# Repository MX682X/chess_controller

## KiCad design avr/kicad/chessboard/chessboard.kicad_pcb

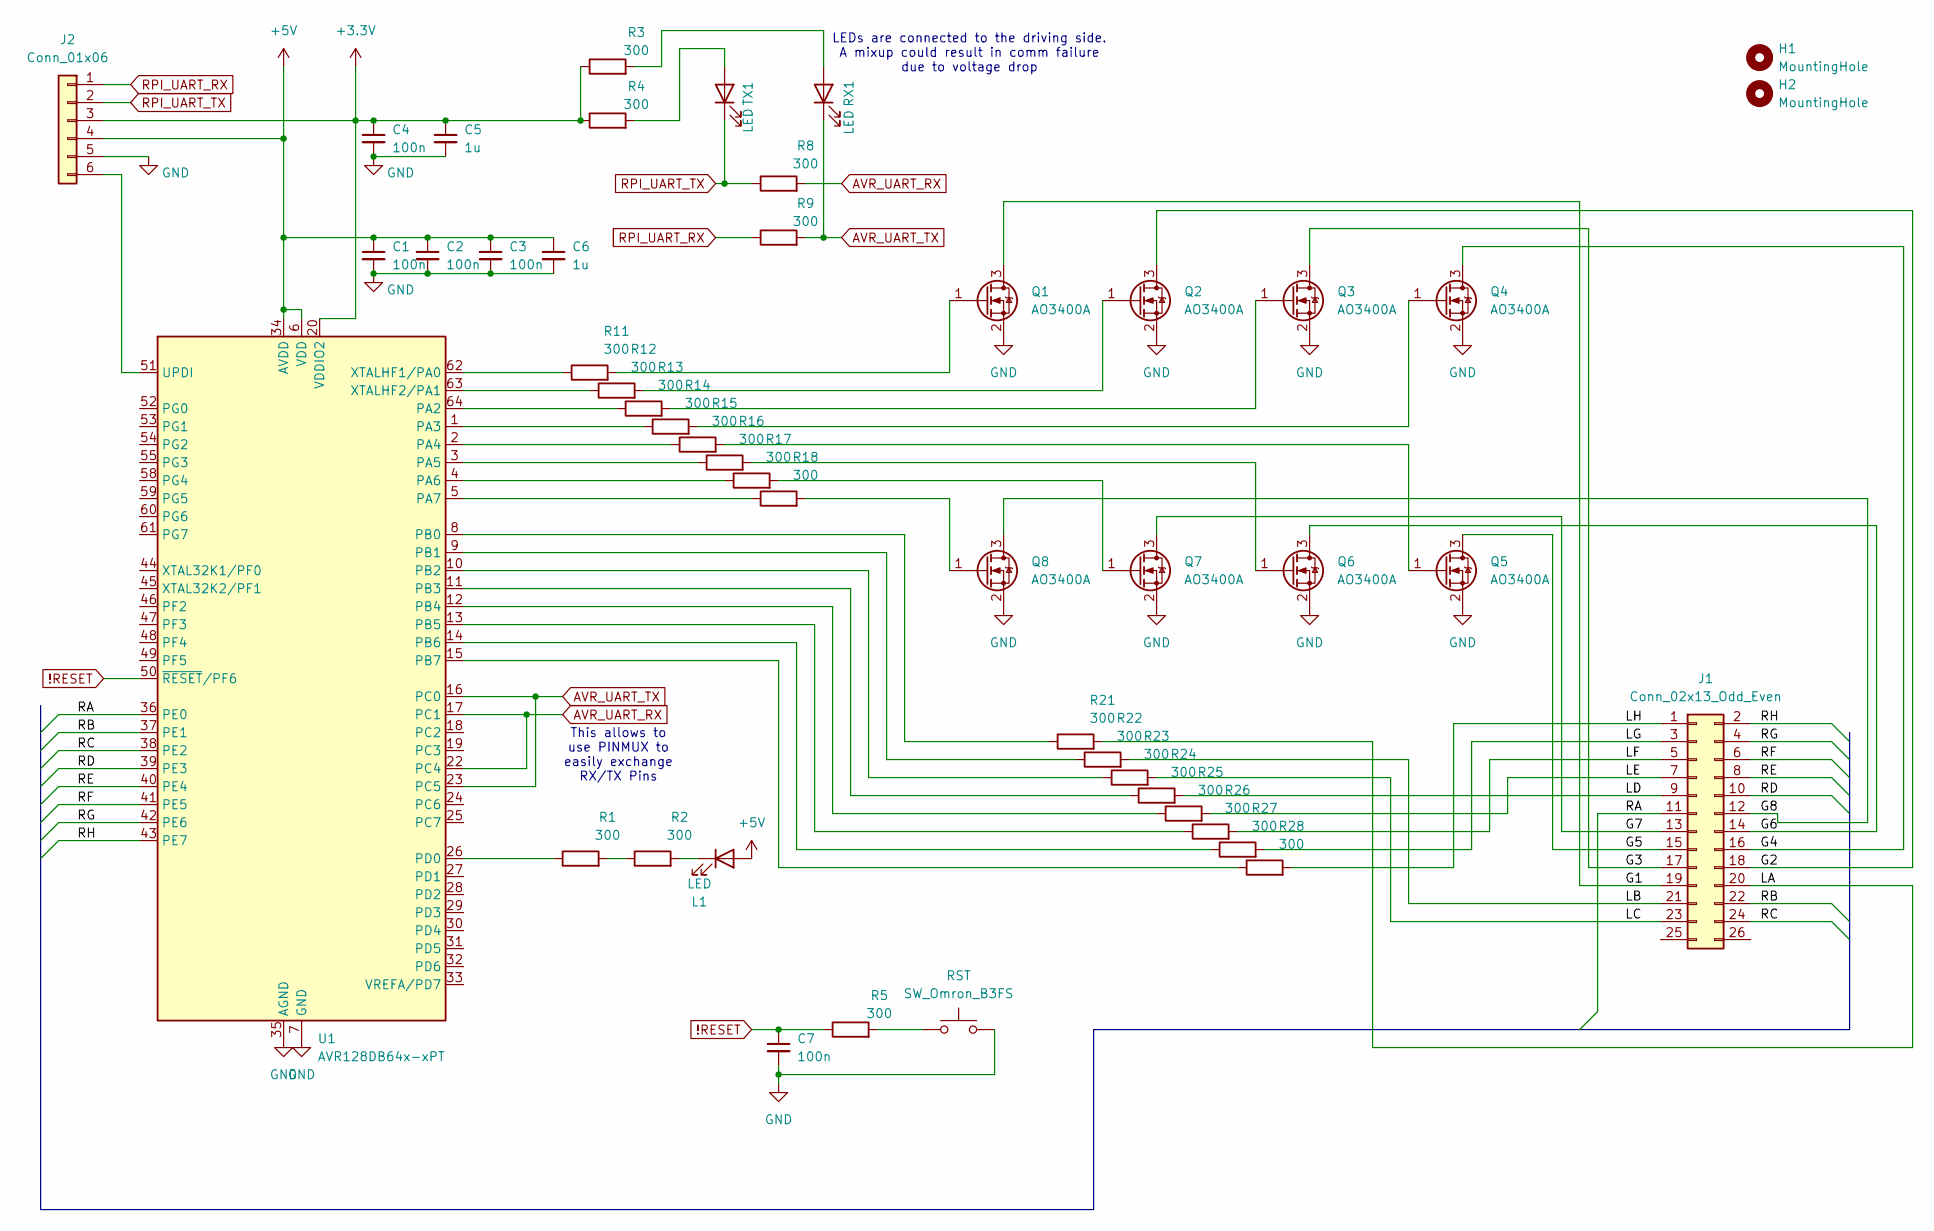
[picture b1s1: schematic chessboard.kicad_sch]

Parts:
C1, C2, C3, C4, C7: 100n; C_0603_1608Metric_Pad1.08x0.95mm_HandSolder
C5, C6: 1u; C_0603_1608Metric_Pad1.08x0.95mm_HandSolder
H1, H2: MountingHole; MountingHole_3.2mm_M3_DIN965
J1: Conn_02x13_Odd_Even; PinHeader_2x13_P2.54mm_Vertical
J2: Conn_01x06; PinSocket_1x06_P2.54mm_Vertical
L1: LED; LED_0603_1608Metric_Pad1.05x0.95mm_HandSolder
Q1, Q2, Q3, Q4, Q5, Q6, Q7, Q8: AO3400A; SOT-23
R1, R2, R3, R4, R5, R8, R9, R11, R12, R13, R14, R15, R16, R17, R18, R21, R22, R23, R24, R25, R26, R27, R28: 300; R_0603_1608Metric_Pad0.98x0.95mm_HandSolder
RST: SW_Omron_B3FS; SW_SPST_Omron_B3FS-100xP
RX1: LED; LED_0603_1608Metric_Pad1.05x0.95mm_HandSolder
TX1: LED; LED_0603_1608Metric_Pad1.05x0.95mm_HandSolder
U1: AVR128DB64x-xPT; TQFP-64_10x10mm_P0.5mm

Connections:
!RESET: C7.1, R5.1, U1.50 (~RESET/PF6)
+3.3V: C4.1, C5.1, J2.3, R3.1, R4.1, U1.20 (VDDIO2)
+5V: C1.1, C2.1, C3.1, C6.1, J2.4, L1.2 (A), U1.6 (VDD), U1.34 (AVDD), U1.56 (VDD)
/G1: J1.19, Q1.3 (D)
/G2: J1.18, Q2.3 (D)
/G3: J1.17, Q3.3 (D)
/G4: J1.16, Q4.3 (D)
/G5: J1.15, Q5.3 (D)
/G6: J1.14, Q6.3 (D)
/G7: J1.13, Q7.3 (D)
/G8: J1.12, Q8.3 (D)
/LA: J1.20, R21.2
/LB: J1.21, R22.2
/LC: J1.23, R23.2
/LD: J1.9, R24.2
/LE: J1.7, R25.2
/LF: J1.5, R26.2
/LG: J1.3, R27.2
/LH: J1.1, R28.2
/RA: J1.11, U1.36 (PE0)
/RB: J1.22, U1.37 (PE1)
/RC: J1.24, U1.38 (PE2)
/RD: J1.10, U1.39 (PE3)
/RE: J1.8, U1.40 (PE4)
/RF: J1.6, U1.41 (PE5)
/RG: J1.4, U1.42 (PE6)
/RH: J1.2, U1.43 (PE7)
AVR_UART_RX: R8.2, U1.17 (PC1), U1.22 (PC4)
AVR_UART_TX: R9.2, RX1.1 (K), U1.16 (PC0), U1.23 (PC5)
GND: C1.2, C2.2, C3.2, C4.2, C5.2, C6.2, C7.2, J2.5, Q1.2 (S), Q2.2 (S), Q3.2 (S), Q4.2 (S), Q5.2 (S), Q6.2 (S), Q7.2 (S), Q8.2 (S), RST.2, U1.7 (GND), U1.21 (GND), U1.35 (AGND), U1.57 (GND)
unnamed: J2.6, U1.51 (UPDI)
unnamed: L1.1 (K), R2.2
unnamed: Q1.1 (G), R11.2
unnamed: Q2.1 (G), R12.2
unnamed: Q3.1 (G), R13.2
unnamed: Q4.1 (G), R14.2
unnamed: Q5.1 (G), R15.2
unnamed: Q6.1 (G), R16.2
unnamed: Q7.1 (G), R17.2
unnamed: Q8.1 (G), R18.2
unnamed: R1.2, R2.1
unnamed: R5.2, RST.1
unnamed: R3.2, RX1.2 (A)
unnamed: R4.2, TX1.2 (A)
unnamed: R13.1, U1.64 (PA2)
unnamed: R14.1, U1.1 (PA3)
unnamed: R15.1, U1.2 (PA4)
unnamed: R16.1, U1.3 (PA5)
unnamed: R17.1, U1.4 (PA6)
unnamed: R18.1, U1.5 (PA7)
unnamed: R21.1, U1.8 (PB0)
unnamed: R22.1, U1.9 (PB1)
unnamed: R23.1, U1.10 (PB2)
unnamed: R24.1, U1.11 (PB3)
unnamed: R25.1, U1.12 (PB4)
unnamed: R26.1, U1.13 (PB5)
unnamed: R27.1, U1.14 (PB6)
unnamed: R28.1, U1.15 (PB7)
unnamed: R1.1, U1.26 (PD0)
unnamed: R11.1, U1.62 (XTALHF1/PA0)
unnamed: R12.1, U1.63 (XTALHF2/PA1)
RPI_UART_RX: J2.1, R9.1
RPI_UART_TX: J2.2, R8.1, TX1.1 (K)

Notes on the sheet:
This allows to use PINMUX to easily exchange RX/TX Pins
LEDs are connected to the driving side. A mixup could result in comm failure due to voltage drop

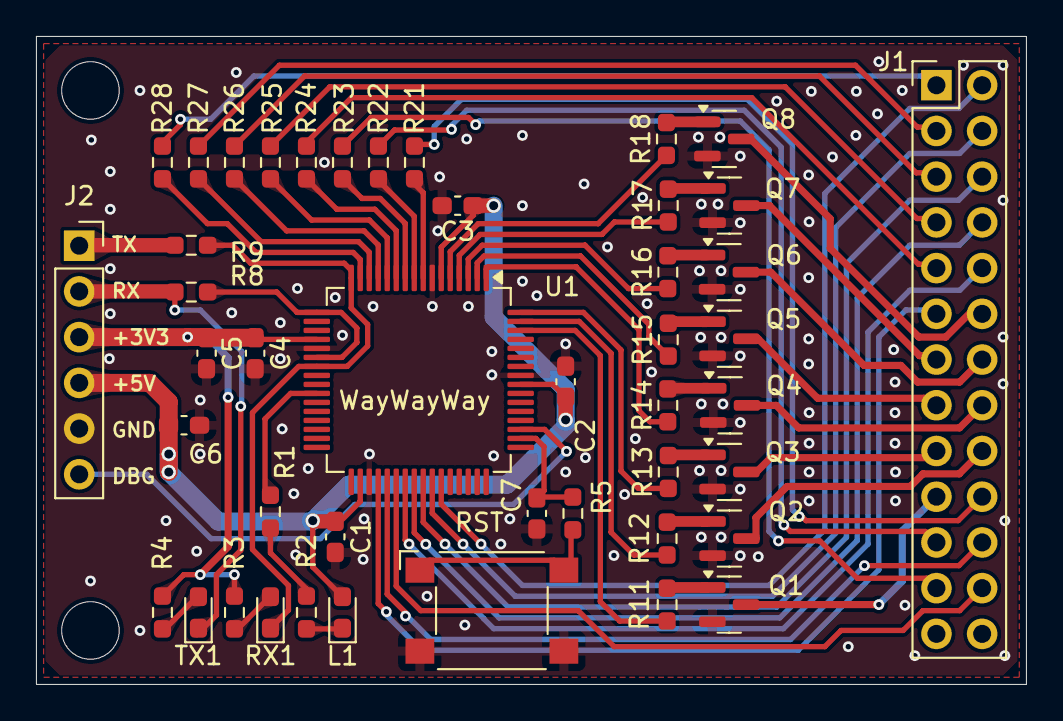
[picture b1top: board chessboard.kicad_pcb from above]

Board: 2 copper layers, 55.0 x 36.0 mm, 47 parts (0 on the bottom side), 63 nets.

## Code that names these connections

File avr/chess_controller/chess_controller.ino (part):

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 * DB-Series
 * AVR64DB64 (optiboot)
 * Clock Speed: 16 MHz, internal
 * Bootloader Serial port: PC0, PC1
 * MVIO: Enabled
 * 
*/ 
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  TCB4.CCMP = 46875;
  TCB4.CTRLA = TCB_CLKSEL_DIV2_gc | TCB_ENABLE_bm;
  
  digitalWriteFast(PIN_PD0, HIGH);  // "disable" LED
  pinConfigure(PIN_PD0, (PIN_DIR_OUT | PIN_INVERT_ON | PIN_ISC_DISABLE));
  digitalWriteFast(PIN_PA0, HIGH);  // init FET loop
  CURR_LINE = 0x00;
  Serial.begin(115200);
  
  Serial.println("Setup Done");
  digitalWriteFast(PIN_PD0, HIGH);  // "Enable" LED

  boot_splash();
}
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    COM_VPORT.OUT = 0x01;             // enable first com transistor
    ACQ_STATUS |= 0x01;               // indicator for "all 8"
    CURR_LINE = 0x00;
    VPORTD.IN |= 0x01;                // activity PD0 (toggle)
  } else {
    LED_VPORT.OUT = current_leds[line];  // load new LED state
    COM_VPORT.OUT = com;              // enable next com transistor
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
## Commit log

2024-10-02 extend gitignore, fix acqusition
2024-10-02 fix commands
2024-10-03 first Python commit
2024-10-04 startpos part 1
2024-10-04 toolbox part 2 (startpos bugged)
2024-10-04 toolbox part 2 (startpos bugged) (again)
2024-10-04 fixed startpos
2024-10-04 startpos moved and changed
2024-10-04 add board to pos
2024-10-06 its alive
2024-10-06 fixed import
2024-10-07 extend command set
2024-10-09 format and match case
2024-10-09 added board simulation gui
2024-10-09 display (untested)
2024-10-10 include display (still untested)
2024-10-14 added CMD Handling (I should really test this)
2024-10-15 fixed CMD Handling (you guessed it: Its still untestet)
2024-10-16 fixed waitforstartpos
2024-10-16 CMD bugfix
2024-10-16 CMD bugfix2
2024-10-16 CMD bugfix 3
2024-10-16 CMD bugfix 4
2024-10-16 CMD bugfix 5
2024-10-16 CMD bugfix 6
2024-10-16 CMD bugfix 7
2024-10-16 CMD bugfix 8
2024-10-16 CMD bugfix 9
2024-10-16 CMD bugfix 10
2024-10-16 CMD bugfix 11
2024-10-16 CMD bugfix 12
2024-10-16 lcd bugfix 1
2024-10-16 lcd bugfix 2
2024-10-16 threading bugfix 1
2024-10-16 threading bugfix 2
2024-10-16 lcd bugfix 3
2024-10-16 lcd bugfix 4
2024-10-16 beauty
2024-10-16 import+display cleanup
2024-10-16 display cleanup (for real)
2024-10-16 added input buffer reset
2024-10-16 reset debug
2024-10-16 reset debuged
2024-10-16 Squash commits
    reset debuged
    reset debug
    added input buffer reset
    display cleanup (for real)
    import+display cleanup
    beauty
2024-10-17 added Playercolors and over Board play
2024-10-23 added pgn export
2024-12-17 first test
2024-12-17 debuging
2024-12-17 debuging 2
2024-12-17 es funktioniert
2024-12-17 implemented stabel command
2024-12-24 cyd init
2024-12-25 added Scene 1_1
2024-12-25 fixed cb functions
2024-12-25 added transition
2025-01-10 added lv config
2025-01-10 new cyd
2025-01-12 added \n
2025-01-12 stopping with exitflag
2025-01-12 idk 4
2025-01-12 idk 5
2025-01-12 changed Displaycommands
2025-01-12 idk7
2025-01-12 implementet display reboot
2025-01-12 implementet display reboot again
2025-01-12 better display
2025-01-15 minifix
2025-01-18 display code for game over
2025-01-18 small fix
2025-01-21 alles neu
2025-01-23 heeeeeeeeey
2025-01-24 readability fix
2025-01-30 descriptions
2025-01-30 new Pictures
2025-01-30 update bootloader to start on swrst
2025-01-30 clean up and adding software reset feature
2025-01-30 finish up enabling software update mode from serial
2025-01-31 fen parsing
2025-01-31 nice
2025-01-31 nice 2
2025-02-01 Scene update 1
2025-02-01 Button update
2025-02-01 fen update
2025-02-01 Documentation Part 1
2025-02-04 untestet start
2025-02-04 increase filter time
2025-02-04 Changed Clock speed
2025-02-04 changed com
2025-02-05 change input level setting
2025-02-07 gui change (display)
2025-02-07 change Skill level
2025-02-07 changed stockfish name in pgn
2025-02-07 set standart roller position
2025-02-08 introduced --fen argument
2025-02-08 Command Classes instead of Command Strings
2025-02-08 moved Commandhandeling to statemachine.py
2025-02-10 implemented nocli argument/flag
2025-02-10 gui finished
2025-02-10 rasp adjusted
2025-02-11 neustart: gui finished
2025-02-24 neustart: implemented Restart Command
2025-03-02 promotion:gui finished
2025-03-02 promotion:implemented command
2025-03-02 Documentation (states)
2025-03-02 promotion: new State
2025-08-04 platformio port
2025-08-04 remove stuff
2025-08-04 renaming functions
